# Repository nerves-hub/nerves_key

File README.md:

# NervesKey

The NervesKey is a configured [ATECC508A or ATECC608A Crypto
Authentication](https://www.microchip.com/wwwproducts/en/ATECC508A) chip that's
used for authenticating devices with NervesHub and other cloud services. At a
high level, it is a simple hardware security module (HSM) that protects one
private key by requiring all operations on that key to occur inside chip. The
project provides access to the chip from Elixir and makes configuration
decisions to make working with the device easier. It has the following features:

1. Provision blank ATECC508A/608A devices - this includes private key generation
2. Storage for serial number and one-time calibration data (useful if primary
   storage is on a removable MicroSD card)
3. Support for Microchip's compressed X.509 certificate format to work with
   Microchip's C libraries
4. Support for signing device certificates so that devices can be included in a
   PKI
5. Support for storing a small amount of run-time configuration in unused data
   EEPROM slots
6. Support auxillary device/signer certificate storage to support pre-production
   experimentation without needing to lock down certificates
7. (bonus) Optionally lock down the hardware device with an activation key. More
   complex but offers a method of storing encryption keys. See Volatile key
   configuration later in this document.

It cannot be stressed enough that the NervesKey library locks down the
ATECC508A/608A during the provisioning process. This is a feature and is
required for normal operation, but if you're getting started, make sure that you
have a few extra parts just in case you make a mistake.

See [NervesHub documentation](https://docs.nerves-hub.org/) for end-user
NervesKey and NervesHub documentation.

See [hw/hw.md](hw/hw.md) for hardware information or go to
[Tindie/NervesKey](https://www.tindie.com/products/troodonsw/nerveskey/) for a
prebuilt-one.
There are a few options for purchase as breakout boards with STEMMA QT / Qwiic 4-Pin JST SH connectors
- Adafruit ATECC608 - https://www.adafruit.com/product/4314
- Sparkfun ATECC508A - https://www.sparkfun.com/products/15573
- Sparkfun ATECC608A - https://www.sparkfun.com/products/15838

Since many of us had a hard time buying ATECC parts, but had a much easier time
buying [ATECC608B Trust and Go](https://www.microchipdirect.com/product/search/all/ATECC608B-TNGTLSU)
parts, this library supports these. The Trust and Go parts come provisioned.
You can still get their serial number and device certificates, though.

## Installation

The package can be installed by adding `nerves_key` to your list of dependencies in `mix.exs`:

```elixir
def deps do
  [
    {:nerves_key, "~> 1.1"}
  ]
end
```

The docs can be found at [https://nerves-key.hexdocs.pm](https://hexdocs.pm/nerves_key).

## General use

NervesKeys need to be provisioned before they can be used. That's a one-time
step that could already have been done for you. If not, see subsequent sections
for how that works.

To use any of the NervesKey APIs, you will need a "transport" to communicate
with the ATECC508A/608A that's doing all of the work. Currently the only
supported transport is I2C. The following line would be run on your Nerves
device (like a Raspberry Pi, BeagleBone or your own custom hardware):

```elixir
iex> {:ok, i2c} = ATECC508A.Transport.I2C.init([])
```

Check if your NervesKey has been provisioned:

```elixir
iex> NervesKey.provisioned?(i2c)
true
```

If you get `false`, go to the provisioning sections. If you received an error,
check that the NervesKey has a good connection to your hardware. If you have a
custom board, you may need to pass parameters to
`ATECC508A.Transport.I2C.init/1` to set the correct I2C bus.

NervesKeys are provisioned with serial numbers. In production, these can be of
your choosing.

```elixir
iex> NervesKey.manufacturer_sn(i2c)
"ABC12345"
```

Of course, the more interesting part of the NervesKeys are its storage of device
private keys and their certificates. For the common case, it stores two X.509
certificates: one for the device and one for the certificate that signed the
device certificate. The signer certificate is usually uploaded to the servers
that the device will connect to so that it can authenticate the device. Here's
how to get both of the certificates:

```elixir
iex> NervesKey.device_cert(i2c)
{:OTPCertificate, ...}

# Put this in a convenient form:
iex> X509.Certificate.to_pem(v()) |> IO.puts
-----BEGIN CERTIFICATE-----
stuff
stuff
stuff
-----END CERTIFICATE-----

iex> NervesKey.signer_cert(i2c)
{:OTPCertificate, ...}
```

The next step is to tell Erlang's SSL library that you want to use the NervesKey
when connecting to the server. For that, you'll need
[nerves_key_pkcs11](https://github.com/nerves-hub/nerves_key_pkcs11) which is
included as a dependency of this library. This code is somewhat tedious but
hopefully the following code fragment will help:

```elixir
   {:ok, engine} = NervesKey.PKCS11.load_engine()
   {:ok, i2c} = ATECC508A.Transport.I2C.init([])

   signer_cert = X509.Certificate.to_der(NervesKey.signer_cert(i2c))
   cert = X509.Certificate.to_der(NervesKey.device_cert(i2c))
   key = NervesKey.PKCS11.private_key(engine, {:i2c, 1})
   cacerts = [signer_cert] ++ Keyword.get(opts, :trusted_certs, [])

   Tortoise.Supervisor.start_child(
     server: {
       Tortoise.Transport.SSL,
       verify: :verify_peer,
       host: Keyword.get(opts, :host),
       cert: cert,
       key: key,
       cacerts: cacerts,
       versions: [:"tlsv1.2"],
     })
```

### Connecting to Google Cloud Platform IoT Core

While the prior `Tortoise` code snippet works well with services like AWS, Google Cloud Platform (GCP) requires that a device must [create a JWT token](https://cloud.google.com/iot/docs/how-tos/credentials/jwts) in order to [connect to the broker](https://cloud.google.com/iot/docs/how-tos/mqtt-bridge#configuring_mqtt_clients). NervesKey provides the `NervesKey.sign_digest` function to assist with the [JWT signature](https://cloud.google.com/iot/docs/how-tos/credentials/jwts#jwt_signature) portion of Google's documentation. The following code fragment can help with creating the JWT that is required as the MQTT password:

```elixir
@doc """
Generate a JSON Web Token used to sign into the Google Cloud Platform
IoT Core MQTT broker.
"""
@spec generate_jwt() :: String.t()
def generate_jwt do
  jwt_expiration_in_hours = 4
  iat = System.os_time(:second)
  exp = iat + jwt_expiration_in_hours * 60 * 60
  aud = Application.get_env(:__my_project__, :gcp_project_id)

  header = %{"alg" => "ES256", "typ" => "JWT"}
  payload = %{"iat" => iat, "exp" => exp, "aud" => aud}

  sign(header, payload)
end

@doc """
Sign a JSON Web Token.
"""
@spec sign(header :: map, payload :: map) :: String.t()
def sign(header, payload) do
  {:ok, transport} = ATECC508A.Transport.I2C.init([])

  encoded_header =
    header
    |> Jason.encode!()
    |> Base.url_encode64(padding: false)

  encoded_payload =
    payload
    |> Jason.encode!()
    |> Base.url_encode64(padding: false)

  digest = :crypto.hash(:sha256, "#{encoded_header}.#{encoded_payload}")
  {:ok, signature} = NervesKey.sign_digest(transport, digest)
  encoded_signature = Base.url_encode64(signature, padding: false)

  "#{encoded_header}.#{encoded_payload}.#{encoded_signature}"
end
```

This fragment can allow for the dependency injection of `sign` if the firmware needs to run both with and without the ATECC crypto chip (i.e. on the target and on the host). [`JOSE.JWT.sign`](https://jose.hexdocs.pm/JOSE.JWT.html#sign/3) can be used for a host implementation.

## Preparing for provisioning

The ATECC508A/608A in the NervesKey needs to be provisioned before it can be
used.  Before you can do that, you'll need the following:

1. A signer certificate and its private certificate (in other contexts, this is
   called a certificate authority)
2. A serial number for your device
3. A name for the device

The signer certificate and serial number are very important. After the
provisioning process, they are locked down and cannot be changed without
replacing the ATECC508A/608A. The device name is purely informational unless you
choose to use it in your software.

NervesKeys support an auxillary set of certificates that identify the device.
These are writable after the provisioning process. Since they're writable, they
can be provisioned and updated at any time. As such, they're not programmed in
the first-time provisioning process.

### Signer certificates

Part of the provisioning process creates an X.509 certificate for the NervesKey
that can be used to authenticate TLS connections. This certificate is signed by
a "signer certificate". You will eventually need to upload the signer
certificate to NervesHub or AWS IoT or wherever you would like to authenticate
devices.

Due to memory limitations, the ATECC508A/608A has a way to compress X.509
certificates on chip. See [ATECC Compressed Certificate
Definition](https://ww1.microchip.com/downloads/en/Appnotes/20006367A.pdf).
To comply with the limitations of compressible certificates, NervesKey provides
a mix task to create them:

```sh
$ mix nerves_key.signer create nerveskey_prod_signer1
Created signer cert, nerveskey_prod_signer1.cert and private key, nerveskey_prod_signer1.key.

Please store nerveskey_prod_signer1.key in a safe place.

nerveskey_prod_signer1.cert is ready to be uploaded to the servers that need
to authenticate devices signed by the private key.
```

There is no magic in the compressible certificates. They're just limited in what
they can contain. You can inspect them with `openssl x509 -in
nerveskey_prod_signer1.cert -text`.

Check with your IoT service on how the signer certificate is used. If it's only
used for first-time device registration, then the signer certificate may not
need a long expiration time. You may also be interested in creating more than
one signer certificate if you have more than one manufacturing facility.

### Manufacturer serial numbers

Be aware that there are a lot of things called serial numbers. In an attempt to
minimize confusion, we'll refer to the serial number that identifies the device
to humans and other machines as the "manufacturer serial number". This string
(it need not be a number) is commonly printed on a label on a device. It may be
embedded in a barcode. Other serial numbers exist - the ATECC508A/608A has a 9
byte one and X.509 certificates have ones. Those serial numbers have guarantees
on uniqueness. It is up to the device manufacturer to make sure that the
"manufacturer serial number" is unique. People generally want to do this for
their own sanity.

The NervesKey saves the manufacturing serial number in the one-time programmable
memory on the ATECC508A/608A and also in the device's X.509 certificate. The
device's X.509 certificate is signed, so cloud servers can trust the
manufacturer serial number.

At this point, you're the manufacturer. Decide how you'd like your serial
numbers to look. Whatever you pick, it must fit in 48-bytes. Representing the
serial number is ASCII is commonly done. If you don't want to deal with this, do
what we do (Base32-encode the ATECC508A/608A's globally unique identifier):

```elixir
iex> {:ok, i2c} = ATECC508A.Transport.I2C.init([])
{:ok, {ATECC508A.Transport.I2C, {#Reference<0.879310498.269090821.27261>, 96}}}
iex> NervesKey.default_info(i2c)
%NervesKey.ProvisioningInfo{
  board_name: "NervesKey",
  manufacturer_sn: "AER245UNQOY4T3Q"
}
```

## Provisioning

Now that you have a signer certificate, the signer's private key, and a
manufacturer serial number, you can provision a NervesKey or the ATECC508A/608A
acting as a NervesKey in your device.  Usually there's some custom manufacturing
support software that performs this step. We'll provision at the iex prompt.

Use `sftp` to copy the signer certificate and private key to your device. We'll
put them `/tmp` so that they disappear on reboot:

```sh
$ sftp nerves.local
Connected to nerves.local.
sftp> cd /tmp
sftp> put nerveskey_prod_signer1.*
Uploading nerveskey_prod_signer1.cert to /tmp/nerveskey_prod_signer1.cert
nerveskey_prod_signer1.cert                                              100%  636    78.3KB/s   00:00
Uploading nerveskey_prod_signer1.key to /tmp/nerveskey_prod_signer1.key
nerveskey_prod_signer1.key                                               100%  228    78.3KB/s   00:00
sftp> exit
```

Next, go to the IEx prompt on the device and run the following:

```elixir
# Customize these or use `NervesKey.default_info/1` for defaults
cert_name="nerveskey_prod_signer1"
manufacturer_sn = "N1234"
board_name = "NervesKey"

# These lines should be copy/paste
signer_cert = File.read!("/tmp/#{cert_name}.cert") |> X509.Certificate.from_pem!;true
signer_key = File.read!("/tmp/#{cert_name}.key") |> X509.PrivateKey.from_pem!();true

{:ok, i2c} = ATECC508A.Transport.I2C.init([])
provision_info = %NervesKey.ProvisioningInfo{manufacturer_sn: manufacturer_sn, board_name: board_name}

# Double-check what you typed above before running this
NervesKey.provision(i2c, provision_info, signer_cert, signer_key)
```

If the last line returns `:ok` after about 2 seconds, then celebrate. You
successfully programmed a NervesKey. You can't program it again. If you try,
you'll get an error.

## Provisioning an auxiliary certificate

If a situation arises where the originally provisioned certificate can't be
used, it's possible to store a second certificate on the device. This second
certificate uses the same private key as the first certificate. (It is assumed
that the algorithmic and physical protections on the first private key are
sufficient that storing two different private keys doesn't add value.) Use cases
include:

1. Recovering from expiration or loss of the original signer key
2. Experimentation
3. Fixing errors in the original certificates

The auxiliary certificate is stored in writable memory on the ATECC508A/608A.

The NervesKey must be provisioned before the auxiliary certificate can be
written. Assuming that's been done, copy the signer certificate and private key
to your device similar to what you did before. Then run the following at the IEx
prompt:

```elixir
# Customize these
cert_name="nerveskey_prod_signer1"

# These lines should be copy/paste
signer_cert = File.read!("/tmp/#{cert_name}.cert") |> X509.Certificate.from_pem!;true
signer_key = File.read!("/tmp/#{cert_name}.key") |> X509.PrivateKey.from_pem!();true

{:ok, i2c} = ATECC508A.Transport.I2C.init([])
NervesKey.provision_aux_certificates(i2c, signer_cert, signer_key)
```

## Debugging without an ATECC508A/608A

Before hardware is available or if you're debugging connections to a service
(like AWS IoT) and having no luck, it can be useful to manually generate
device certificates. The `nerves_key.device` helper can be used for this and
does not require a NervesKey at all. Certificates generated using this helper
will look like ones stored on the NervesKey except for the important feature of
the private key part being private.

Here's an example:

```sh
mix nerves_key.device create <serial number> --signer-cert ca.cert --signer-key ca.key
```

Just like the signer certs, you can inspect the generated certs with `openssl
x509`. Services that work with these certificates should work with real
NervesKeys.

## Settings

The NervesKey has bytes left over for storing a few settings. The
`NervesKey.put_settings/2` and `NervesKey.get_settings/1` APIs let you store and
retrieve a map. Since the storage is limited and relatively slow, this is
intended for settings that rarely change or may be tightly coupled with
certificates already being stored in the NervesKey.

Internally, `NervesKey` calls `:erlang.term_to_binary` to convert the map to raw
bytes and then it spreads it across ATECC508A slots for storage. This means that
the keys used in the map take up space too.

## Support

If you run into problems, please help us improve this project by filing an
[issue](https://github.com/nerves-hub/nerves_key/issues/new).

## ATECC508A configuration

This section describes the ATECC508A/608A configuration used for the
[NervesKey](https://github.com/nerves-hub/nerves_key). This information isn't
needed for using the library.

See Table 2-5 in the ATECC508A data sheet for documentation on the configuration
zone.  This software expects the following configuration to be programmed
(unspecified bytes are either not programmable or kept as their defaults):

Bytes  | Name        | Value  | Description
-----  | ----------- | ------ | -----------
14     | I2C_Enable  | 01     | I2C mode
16     | I2C_Address | C0     | I2C address of the module (default)
18     | OTPmode     | AA     | OTP is in read-only mode
19     | ChipMode    | 00     | Default mode
20-51  | SlotConfig  | N/A    | See the next table
92-95  | X509Format  | 00..00 | Unused
96-127 | KeyConfig   | N/A    | See next table

The slots are programmed as follows. This definition is organized to be similar
to the Microchip Standard TLS Configuration to minimize changes to other
software. Unused slots are configured so that applications can use them as they
would an EEPROM.

Slot | Description              | SlotConfig | KeyConfig | Primary properties
---- | ------------------------ | ---------- | --------- | ------------------
0    | Device private key       | 87 20      | 33 00     | Private key, read only; lockable
1    | Unused                   | 0F 0F      | 1C 00     | Clear read/write; not lockable
2    | Unused                   | 0F 0F      | 1C 00     | Clear read/write; not lockable
3    | Unused                   | 0F 0F      | 1C 00     | Clear read/write; not lockable
4    | Unused                   | 0F 0F      | 1C 00     | Clear read/write; not lockable
5    | Settings (Part 3)        | 0F 0F      | 1C 00     | Clear read/write; not lockable
6    | Settings (Part 2)        | 0F 0F      | 1C 00     | Clear read/write; not lockable
7    | Settings (Part 1)        | 0F 0F      | 1C 00     | Clear read/write; not lockable
8    | Settings (Part 0)        | 0F 0F      | 3C 00     | Clear read/write; lockable
9    | Aux device certificate   | 0F 0F      | 3C 00     | Clear read/write; lockable
10   | Device certificate       | 0F 2F      | 3C 00     | Clear read only; lockable
11   | Signer public key        | 0F 2F      | 30 00     | P256; Clear read only; lockable
12   | Signer certificate       | 0F 2F      | 3C 00     | Clear read only; lockable
13   | Signer serial number +   | 0F 2F      | 3C 00     | Clear read only; lockable
14   | Aux signer public key    | 0F 0F      | 3C 00     | Clear read/write; lockable
15   | Aux signer certificate   | 0F 0F      | 3C 00     | Clear read/write; lockable

+ The signer serial number slot is currently unused since the signer's cert is
  computed from the public key

The ATECC508A includes a 64 byte OTP (one-time programmable) memory. It has the
following layout:

Bytes  | Name              | Contents
------ | ----------------- | -------------------------
0-3    | Magic             | 4e 72 76 73
4      | Flags_MSB         | 0
5      | Flags_LSB         | 0 = 16 byte serial number, 1 = 32 byte serial number
6-15   | Board name        | 10 byte name for the board in ASCII (set unused bytes to 0)
16-31  | Mfg serial number | Serial number in ASCII (set unused bytes to 0)
32-63  | Serial# or User   | If Flags == 1, then the rest of the serial number

## ATECC608 volatile key configuration

Volatile key configuration is an option for the ATECC608 chips (A & B). You can reference
[a datasheet here](https://ww1.microchip.com/downloads/en/DeviceDoc/ATECC608A-TFLXTLS-CryptoAuthentication-Data-Sheet-DS40002138A.pdf)
but it does not describe all the features. If you find anywhere that Microchip publishes
the datasheet including the Volatile Key functionality we'd love to reference it properly.

This is an alternate but largely compatible configuration of the NervesKey intended to
add additional security features. It uses two major features of the ATECC608 that the
508 does not fully support. The Volatile Key config and the Persistent Latch.

The configuration sets up an "activation key" (AES, so any 16 bytes should do) in key slot 1
as the key to unlock operation of the chip. It also sets up an "encryption key" (also AES)
in slot 2. These keys are generated outside the chip but also locked into the chip during
provisioning. The NervesKey Device Private Key (slot 0) and Encryption Key (slot 2) will be
disabled until the host demonstrates that it has access to the Activation Key. It requires
authorization. Once authorization is given the chip is fully enabled and can be used as a
regular NervesKey for mTLS and such. The Encryption Key can also be used to derive other keys
such as disk encryption or database encryption keys.

It will maintain this authorization using the Persistent Latch. A bit that is persisted as long
as the device has power. If power is lost authorization goes away and the NervesKey can not be
used when power is restored unless the authorization is provided again. This allows hooking it
up to tamper protection in various ways.

The ATECC608 has *severe limitations* in protecting symmetric encryption keys. The AES feature
passes decrypted information in cleartext over I2C. This configuration is an option for cases
where you want that higher level of security and are willing to trade off on convenience.

**Important:** If you cannot secure the physical aspect with some kind of tamper mechanism,
this config adds complexity but really only provides obscurity. With proper tamper protection,
this should provide reasonable protection for secrets like disk encryption keys. If your board
has other secure storage via ARM TrustZone or similar you don't need this mechanism. With the
appropriate physical and electronic protections in place this can add key storage to a
Raspberry Pi which lacks protected storage.

Providing authorization is up to the application but could be done with a PIN-code, password,
USB key or something else.

Bytes  | Name                  | Value  | Description
-----  | --------------------- | ------ | -----------
14     | I2C_Enable            | 01     | I2C mode
16     | I2C_Address           | C0     | I2C address of the module (default)
18     | OTPmode               | AA     | OTP is in read-only mode
19     | ChipMode              | 00     | Default mode
20-51  | SlotConfig            | N/A    | See the next table
69     | VolatileKeyPermission | 81     | VolKeyPermitSlot=1, VolKeyPermitEnable=true
92-95  | X509Format            | 00..00 | Unused
96-127 | KeyConfig             | N/A    | See next table

The slots are programmed as follows. This definition is organized to be similar
to the Microchip Standard TLS Configuration to minimize changes to other
software. It only differs from the base NervesKey in disabling the private key until authorized
and including an AES key for use with deriving secrets.

Slot | Description              | SlotConfig | KeyConfig | Primary properties
---- | ------------------------ | ---------- | --------- | ------------------
0    | Device private key       | 87 20      | 33 10     | Private key, read only; lockable; persistent disable
1    | Activation key           | 81 90      | 78 00     | AES key, require RNG
2    | Encryption key           | 81 90      | 38 10     | AES key, persistent disable
3    | Unused                   | 0F 0F      | 1C 00     | Clear read/write; not lockable
4    | Unused                   | 0F 0F      | 1C 00     | Clear read/write; not lockable
5    | Settings (Part 3)        | 0F 0F      | 1C 00     | Clear read/write; not lockable
6    | Settings (Part 2)        | 0F 0F      | 1C 00     | Clear read/write; not lockable
7    | Settings (Part 1)        | 0F 0F      | 1C 00     | Clear read/write; not lockable
8    | Settings (Part 0)        | 0F 0F      | 3C 00     | Clear read/write; lockable
9    | Aux device certificate   | 0F 0F      | 3C 00     | Clear read/write; lockable
10   | Device certificate       | 0F 2F      | 3C 00     | Clear read only; lockable
11   | Signer public key        | 0F 2F      | 30 00     | P256; Clear read only; lockable
12   | Signer certificate       | 0F 2F      | 3C 00     | Clear read only; lockable
13   | Signer serial number +   | 0F 2F      | 3C 00     | Clear read only; lockable
14   | Aux signer public key    | 0F 0F      | 3C 00     | Clear read/write; lockable
15   | Aux signer certificate   | 0F 0F      | 3C 00     | Clear read/write; lockable

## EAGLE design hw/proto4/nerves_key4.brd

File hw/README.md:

# Hardware

The NervesKey is a tiny circuit board with an ATECC608A cryptographic chip from Microchip Technology. The chip is a relatively inexpensive addition to embedded computing platforms that include an I2C bus. The NervesKey is primarily intended to offer a non-disruptive adaptation for the Raspberry Pi, but can also be used in other development applications.

**Figure 1**  Assembled NervesKey Boards

This directory contains hardware documentation for the production NervesKey board.  Historical versions from earlier development efforts are removed to avoid confusion, but in general those will operate the same way.  Some historical versions might contain the ATECC508A chip instead, but the NervesKey software is agnostic 
to this difference.  

The production NervesKey board contains the tiny 'UDFN' version of the part  [ATECC608A-MAHDA](https://www.digikey.com/product-detail/en/microchip-technology/ATECC608A-MAHDA-S/ATECC608A-MAHDA-STR-ND/7928113) and a 0.1uF 0402 size capacitor.  These boards are not easy assembled by a user, so they are professionally manufactured in high quantity for the Nerves project and offered for sale in low quantity by Nerves contributor [Troodon Software, LLC](http://www.troodon-software.com/).  

## Primary Application - Bottom Side Solder Attach To Raspberry Pi

The easiest way to outfit a Raspberry Pi with a NervesKey is to solder it to the 'hat' expansion header on the bottom of the board as shown below.  This will connect the appropriate signals and keep the board out of the way of other uses of the hat header.  The NervesKey board is made relatively thin to support this application.

**Figure 2**  Primary NervesKey Application

See the [schematic](TSW19001_NERVESKEY_X1_SCH.PDF) for additional hardware details, notes, and examples.

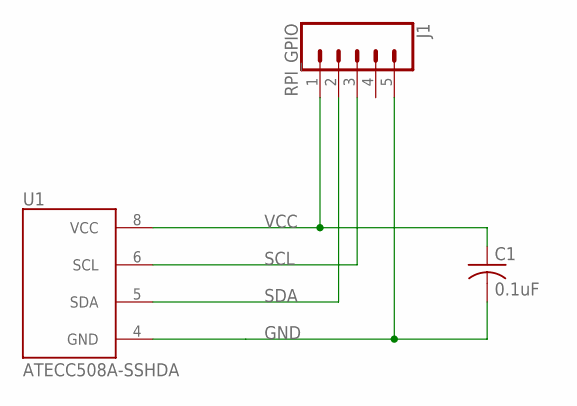
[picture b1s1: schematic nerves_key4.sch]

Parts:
C1: 0.1uF; C0603
J1: RPI_GPIO; 1X05
U1: ATECC508A-SSHDA; SOIC127P625X175-8

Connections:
GND: C1.2, J1.5, U1.4 (GND)
SCL: J1.3, U1.6 (SCL)
SDA: J1.2, U1.5 (SDA)
VCC: C1.1, J1.1, U1.8 (VCC)

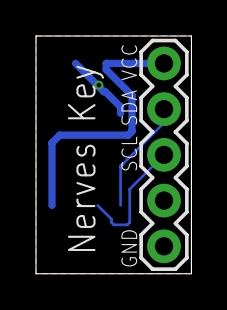
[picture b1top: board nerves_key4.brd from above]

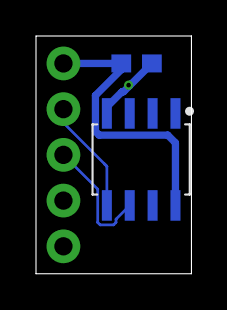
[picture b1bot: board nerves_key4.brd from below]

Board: 2 copper layers, 8.6 x 13.2 mm, 3 parts (2 on the bottom side), 4 nets.

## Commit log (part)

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2018-10-15 Add some docs
2018-10-16 Add function to check that date encodes
2018-10-17 Fix CRC calculation
2018-10-25 Add support for compressing / decompressing certificate
2018-11-14 Refactor unit tests
2018-11-14 More refactoring to support ECC508A cert gen
2018-11-15 Config zone read works
2018-11-16 More WIP
2018-11-20 Refactor transport and use mock to test
2018-11-21 Add pretty form for the configuration
2018-11-28 Configuration and locking the config works
2018-11-28 Fix dialyzer errors
2018-11-29 Move NervesKey configuration to config.ex
2018-12-04 Move to template-driven cert compression
2018-12-05 Provisioning works up to the point of locking
2018-12-05 Fix all but the lock dialyzer issue
2018-12-06 Support ECDH responses in the clear on I2C
2018-12-11 Rename to nerves_key
2018-12-11 Bump Elixir version on CI
2018-12-13 Remove old references to atecc508a app
2018-12-13 Update NervesKey provision to fix execution_error
2018-12-13 Add NervesKey.device_cert/1 for reading the device certificate
2018-12-13 Add NervesHub.signer_cert for reading the signer certificate
2018-12-13 Pull atecc508a from hex
2018-12-14 Encode the public_key before deriving the authority key id
2018-12-15 Fix Markdown lint warnings
2018-12-17 Bump deps
2018-12-17 Improve docs and error messages - especially for certs
2019-01-07 Correct matching of config slot
    slot_config_compatible() did not match on the correct values of slots
    10, 11,12, and 13.
2019-01-08 Add support for specifying signer key expiration
2019-01-14 Add hardware design files
2019-01-21 Support a second set of device/signer certs
    It's sometimes necessary to have a device certificate that can be
    updated after provisioning. This adds support. It is not a default and
    should not be used unless explicitly requested.
2019-01-21 Refer to the ATECC508A/60A consistently
2019-01-23 Add NervesKey defaults for the serial number
    These defaults will be used for pre-programmed NervesKeys.
2019-02-06 v0.3.2 release
2019-02-07 Add NervesKey.detected?/1
2019-02-22 Fix dialyzer issues
2019-03-29 Update for production version
    Reconfigured hardware directory to reflect production version hardware
2019-05-20 Fix rendering of tables with earmark
2019-05-21 Include nerves_key_pkcs11 as a dependency
    Pretty much everyone needs to use nerves_key_pkcs11 so include it as a
    dependency to avoid the error where you forget to add it or misspell it.
2019-05-21 Add device_sn/1 spec
2019-05-22 Add NervesHub doc link; minor edits
2019-10-16 Update links for pre-built modules
2019-10-17 Add ssl_opts helper to simplify integrations
    This saves boilerplate code when using a NervesKey with libraries that
    use TLS like NervesHub, Tortoise, etc.
2020-04-14 Bump deps locally and on CI
2020-05-12 Add nerves_key.device helper
2020-10-29 CI: bump Elixir version
2020-11-02 Move :crypto to :extra_applications
    This library calls :crypto directly, so make sure that it's a direct
    dependency. This shouldn't have ever caused an issue since `:x509`
    depends on it too.
    This also removes `:logger` from the dependencies since this library
    doesn't use it.
2020-11-02 Force nerves_key_pkcs11 v0.2.x
2020-12-09 Added an option for a prebuilt NervesKey alternative
    Some of us live outside of the US and ordering a NervesKey from Tindie is costly and time consuming. I found Adafruit has a breakout board and I was able to buy through a European distributor with ea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
2021-05-20 Bump all dependencies
2021-05-20 Always report compiler warnings as errors
2021-05-27 Add sign_digest/2.
2021-05-28 v0.5.5 release
2021-10-23 Bump dependencies
2022-01-14 Fix manufacturer_sn with trust and go
2022-02-11 Update README.md
    Corrected the Compressed Certificate Definition Hyperlink
2022-02-26 use the trust and go MAC for the alt name, not the serial number
2022-03-01 mix format pass
2022-03-02 v1.1.0 release
2022-06-21 Add note about T&G parts
2023-07-02 Remove unused config.exs
2023-07-02 Update Dialyzer ignore strings
2023-07-02 v1.2.0 release
2023-10-23 Bump dialyxir from 1.3.0 to 1.4.2
    Bumps [dialyxir](https://github.com/jeremyjh/dialyxir) from 1.3.0 to 1.4.2.
    - [Release notes](https://github.com/jeremyjh/dialyxir/releases)
    - [Changelog](https://github.com/jeremyjh/dialyxir/blob/master/CHANGELOG.md)
    - [Commits](https://github.com/jeremyjh/dialyxir/compare/1.3.0...1.4.2)
    ---
    updated-dependencies:
2023-10-24 Bump atecc508a from 1.2.0 to 1.2.1
    Bumps [atecc508a](https://github.com/nerves-hub/atecc508a) from 1.2.0 to 1.2.1.
    - [Release notes](https://github.com/nerves-hub/atecc508a/releases)
    - [Changelog](https://github.com/nerves-hub/atecc508a/blob/main/CHANGELOG.md)
    - [Commits](https://github.com/nerves-hub/atecc508a/compare/v1.2.0...v1.2.1)
    ---
    updated-dependencies:
2023-11-27 implement simple caching mechanism for device and signer cert
2023-12-29 Bump dialyxir from 1.4.2 to 1.4.3
    Bumps [dialyxir](https://github.com/jeremyjh/dialyxir) from 1.4.2 to 1.4.3.
    - [Release notes](https://github.com/jeremyjh/dialyxir/releases)
    - [Changelog](https://github.com/jeremyjh/dialyxir/blob/master/CHANGELOG.md)
    - [Commits](https://github.com/jeremyjh/dialyxir/compare/1.4.2...1.4.3)
    ---
    updated-dependencies:
2024-03-06 Bump ex_doc from 0.31.1 to 0.31.2
    Bumps [ex_doc](https://github.com/elixir-lang/ex_doc) from 0.31.1 to 0.31.2.
    - [Release notes](https://github.com/elixir-lang/ex_doc/releases)
    - [Changelog](https://github.com/elixir-lang/ex_doc/blob/main/CHANGELOG.md)
    - [Commits](https://github.com/elixir-lang/ex_doc/compare/v0.31.1...v0.31.2)
    ---
    updated-dependencies:
2024-04-15 Bump ex_doc from 0.31.2 to 0.32.1
    Bumps [ex_doc](https://github.com/elixir-lang/ex_doc) from 0.31.2 to 0.32.1.
    - [Release notes](https://github.com/elixir-lang/ex_doc/releases)
    - [Changelog](https://github.com/elixir-lang/ex_doc/blob/main/CHANGELOG.md)
    - [Commits](https://github.com/elixir-lang/ex_doc/compare/v0.31.2...v0.32.1)
    ---
    updated-dependencies:
2024-05-30 Bump ex_doc from 0.33.0 to 0.34.0
    Bumps [ex_doc](https://github.com/elixir-lang/ex_doc) from 0.33.0 to 0.34.0.
    - [Release notes](https://github.com/elixir-lang/ex_doc/releases)
    - [Changelog](https://github.com/elixir-lang/ex_doc/blob/main/CHANGELOG.md)
    - [Commits](https://github.com/elixir-lang/ex_doc/compare/v0.33.0...v0.34.0)
    ---
    updated-dependencies:
2024-06-20 Bump ex_doc from 0.34.0 to 0.34.1
    Bumps [ex_doc](https://github.com/elixir-lang/ex_doc) from 0.34.0 to 0.34.1.
    - [Release notes](https://github.com/elixir-lang/ex_doc/releases)
    - [Changelog](https://github.com/elixir-lang/ex_doc/blob/main/CHANGELOG.md)
    - [Commits](https://github.com/elixir-lang/ex_doc/compare/v0.34.0...v0.34.1)
    ---
    updated-dependencies:
2024-09-30 Bump dialyxir from 1.4.3 to 1.4.4
    Bumps [dialyxir](https://github.com/jeremyjh/dialyxir) from 1.4.3 to 1.4.4.
    - [Release notes](https://github.com/jeremyjh/dialyxir/releases)
    - [Changelog](https://github.com/jeremyjh/dialyxir/blob/master/CHANGELOG.md)
    - [Commits](https://github.com/jeremyjh/dialyxir/compare/1.4.3...1.4.4)
    ---
    updated-dependencies:
2024-11-21 Bump ex_doc from 0.35.0 to 0.35.1
    Bumps [ex_doc](https://github.com/elixir-lang/ex_doc) from 0.35.0 to 0.35.1.
    - [Release notes](https://github.com/elixir-lang/ex_doc/releases)
    - [Changelog](https://github.com/elixir-lang/ex_doc/blob/v0.35.1/CHANGELOG.md)
    - [Commits](https://github.com/elixir-lang/ex_doc/compare/v0.35.0...v0.35.1)
    ---
    updated-dependencies:
2025-02-05 Bump ex_doc from 0.36.1 to 0.37.0
    Bumps [ex_doc](https://github.com/elixir-lang/ex_doc) from 0.36.1 to 0.37.0.
    - [Release notes](https://github.com/elixir-lang/ex_doc/releases)
    - [Changelog](https://github.com/elixir-lang/ex_doc/blob/main/CHANGELOG.md)
    - [Commits](https://github.com/elixir-lang/ex_doc/compare/v0.36.1...v0.37.0)
    ---
    updated-dependencies:
2025-02-19 Bump ex_doc from 0.37.1 to 0.37.2
    Bumps [ex_doc](https://github.com/elixir-lang/ex_doc) from 0.37.1 to 0.37.2.
    - [Release notes](https://github.com/elixir-lang/ex_doc/releases)
    - [Changelog](https://github.com/elixir-lang/ex_doc/blob/main/CHANGELOG.md)
    - [Commits](https://github.com/elixir-lang/ex_doc/compare/v0.37.1...v0.37.2)
    ---
    updated-dependencies:
2025-03-09 Bump CI and deps to latest
2025-03-26 Bump atecc508a from 1.3.0 to 1.3.1
    Bumps [atecc508a](https://github.com/nerves-hub/atecc508a) from 1.3.0 to 1.3.1.
    - [Release notes](https://github.com/nerves-hub/atecc508a/releases)
    - [Changelog](https://github.com/nerves-hub/atecc508a/blob/main/CHANGELOG.md)
    - [Commits](https://github.com/nerves-hub/atecc508a/compare/v1.3.0...v1.3.1)
    ---
    updated-dependencies:
2025-05-27 Bump ex_doc from 0.37.3 to 0.38.2
    Bumps [ex_doc](https://github.com/elixir-lang/ex_doc) from 0.37.3 to 0.38.2.
    - [Release notes](https://github.com/elixir-lang/ex_doc/releases)
    - [Changelog](https://github.com/elixir-lang/ex_doc/blob/main/CHANGELOG.md)
    - [Commits](https://github.com/elixir-lang/ex_doc/compare/v0.37.3...v0.38.2)
    ---
    updated-dependencies:
2025-08-19 Bump ex_doc from 0.37.3 to 0.38.3
    Bumps [ex_doc](https://github.com/elixir-lang/ex_doc) from 0.37.3 to 0.38.3.
    - [Release notes](https://github.com/elixir-lang/ex_doc/releases)
    - [Changelog](https://github.com/elixir-lang/ex_doc/blob/main/CHANGELOG.md)
    - [Commits](https://github.com/elixir-lang/ex_doc/compare/v0.37.3...v0.38.3)
    ---
    updated-dependencies:
2025-08-25 Bump deps to latest
2025-08-25 Enable standard dialyzer warnings
2025-08-25 Run REUSE scripts
2025-09-09 Bump ex_doc from 0.38.3 to 0.38.4
    Bumps [ex_doc](https://github.com/elixir-lang/ex_doc) from 0.38.3 to 0.38.4.
    - [Release notes](https://github.com/elixir-lang/ex_doc/releases)
    - [Changelog](https://github.com/elixir-lang/ex_doc/blob/main/CHANGELOG.md)
    - [Commits](https://github.com/elixir-lang/ex_doc/compare/v0.38.3...v0.38.4)
    ---
    updated-dependencies:
2025-10-15 Fix typo and rewrap
2025-10-24 Bump ex_doc from 0.38.3 to 0.39.1
    Bumps [ex_doc](https://github.com/elixir-lang/ex_doc) from 0.38.3 to 0.39.1.
    - [Release notes](https://github.com/elixir-lang/ex_doc/releases)
    - [Changelog](https://github.com/elixir-lang/ex_doc/blob/main/CHANGELOG.md)
    - [Commits](https://github.com/elixir-lang/ex_doc/commits)
    ---
    updated-dependencies:
2025-12-04 Bump ex_doc from 0.38.3 to 0.39.2
    Bumps [ex_doc](https://github.com/elixir-lang/ex_doc) from 0.38.3 to 0.39.2.
    - [Release notes](https://github.com/elixir-lang/ex_doc/releases)
    - [Changelog](https://github.com/elixir-lang/ex_doc/blob/main/CHANGELOG.md)
    - [Commits](https://github.com/elixir-lang/ex_doc/compare/v0.38.3...v0.39.2)
    ---
    updated-dependencies:
2025-12-26 Bump credo from 1.7.12 to 1.7.15
    Bumps [credo](https://github.com/rrrene/credo) from 1.7.12 to 1.7.15.
    - [Release notes](https://github.com/rrrene/credo/releases)
    - [Changelog](https://github.com/rrrene/credo/blob/master/CHANGELOG.md)
    - [Commits](https://github.com/rrrene/credo/compare/v1.7.12...v1.7.15)
    ---
    updated-dependencies:
2026-01-22 Bump all deps and format for Elixir 1.19
2026-03-04 Bump credo from 1.7.15 to 1.7.17
    Bumps [credo](https://github.com/rrrene/credo) from 1.7.15 to 1.7.17.
    - [Release notes](https://github.com/rrrene/credo/releases)
    - [Changelog](https://github.com/rrrene/credo/blob/master/CHANGELOG.md)
    - [Commits](https://github.com/rrrene/credo/compare/v1.7.15...v1.7.17)
    ---
    updated-dependencies:

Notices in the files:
parts and their libraries:
SparkFun-Connectors: Licensing: Creative Commons ShareAlike 4.0 International - https://creativecommons.org/licenses/by-sa/4.0
